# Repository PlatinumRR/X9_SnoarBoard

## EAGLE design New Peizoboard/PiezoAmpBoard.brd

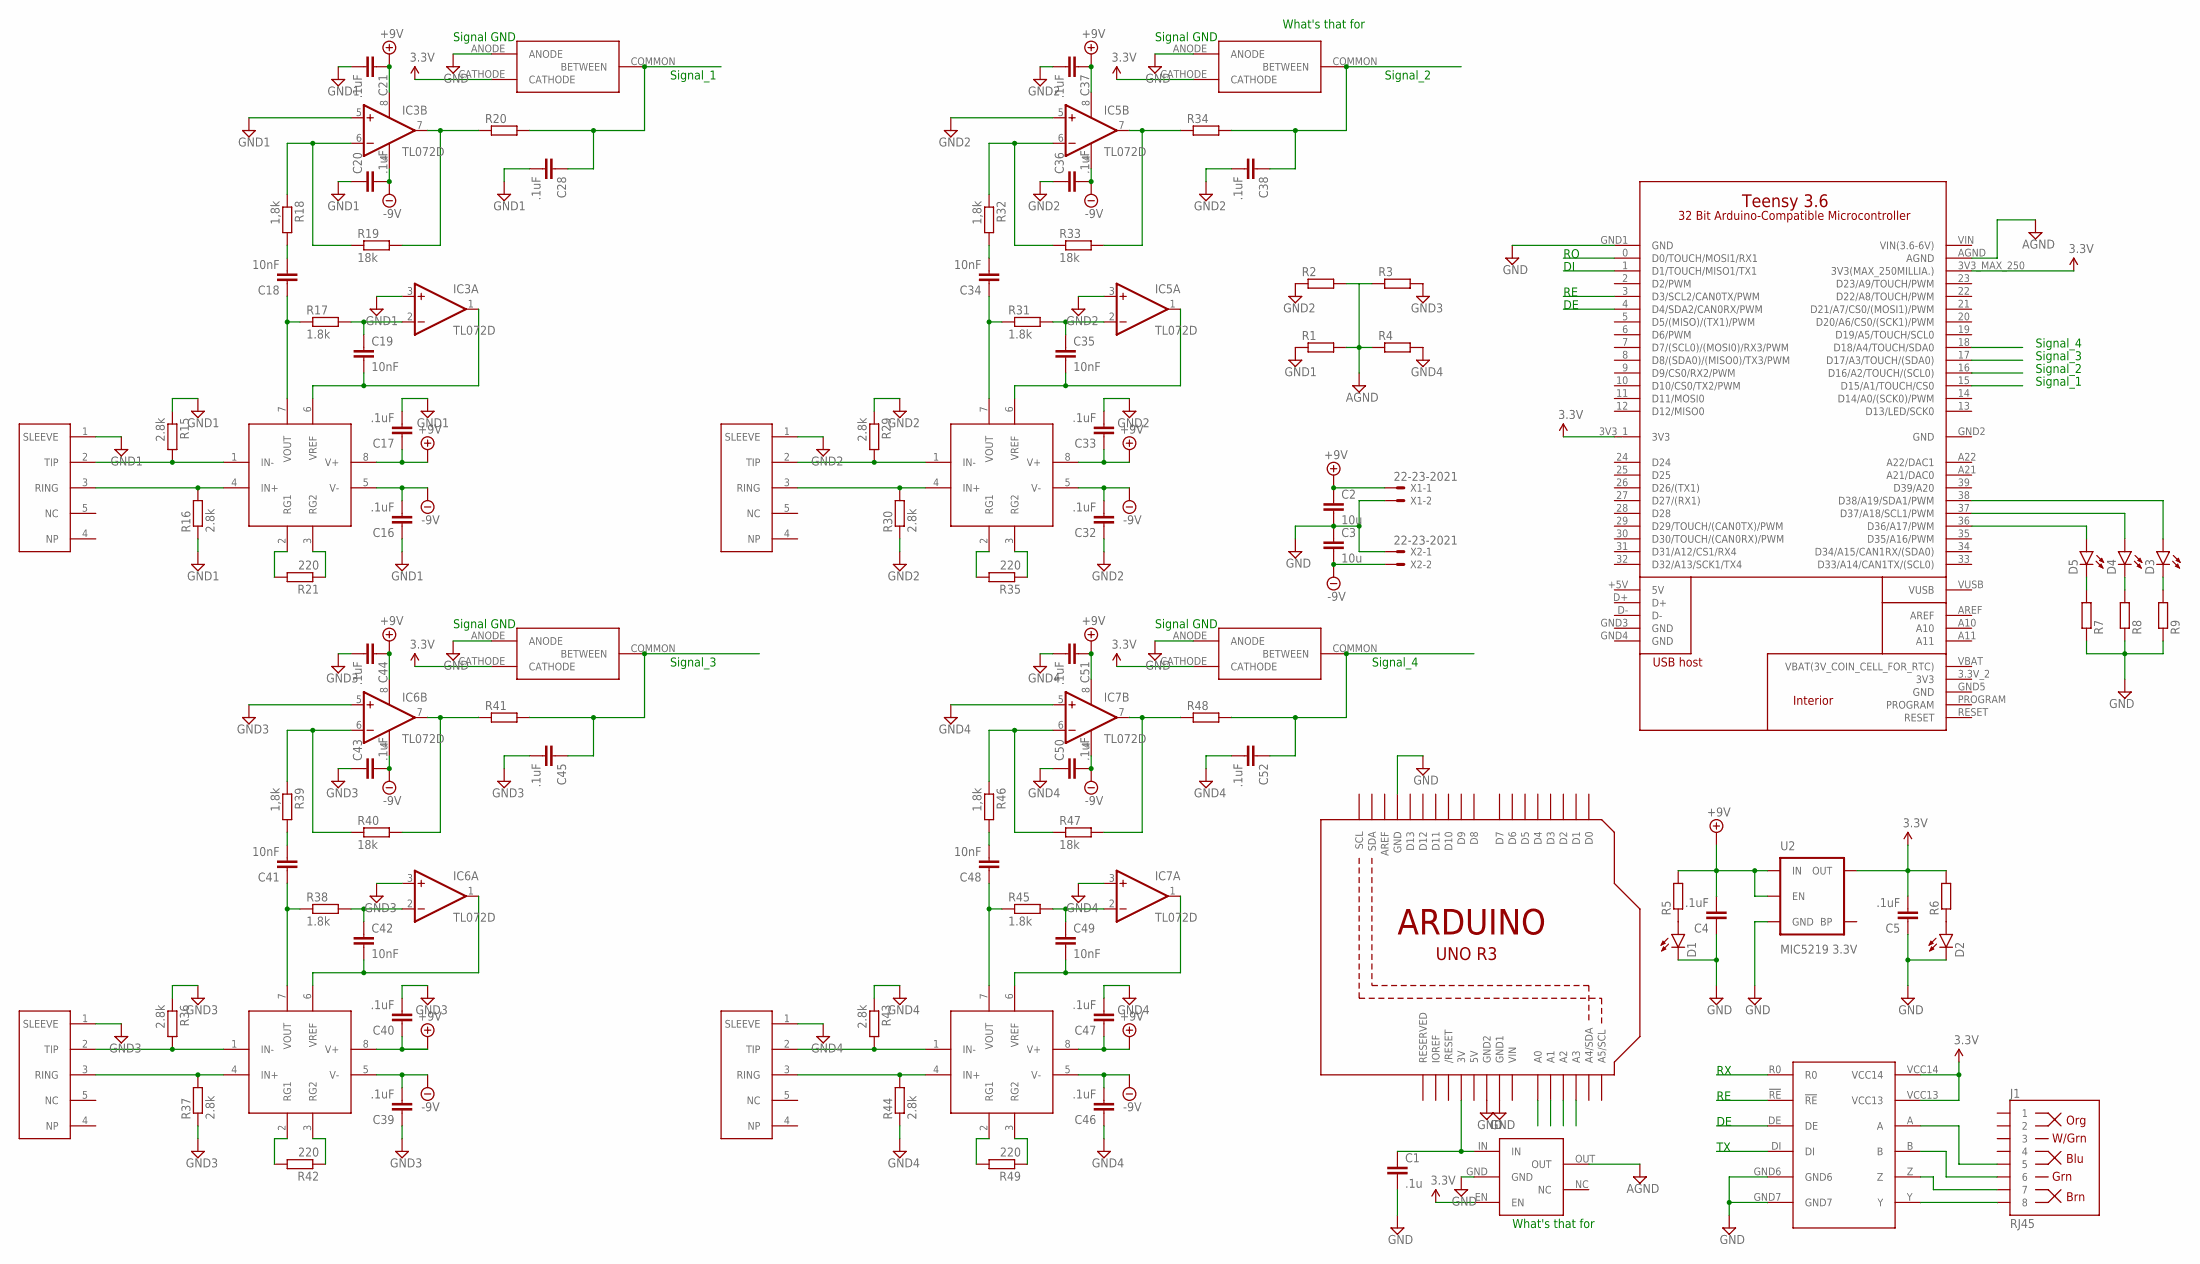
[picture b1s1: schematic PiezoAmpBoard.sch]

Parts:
C1: .1u; C0603
C2, C3: 10u; C0603
C4, C5, C16, C17, C20, C21, C28, C32, C33, C36, C37, C38, C39, C40, C43, C44, C45, C46, C47, C50, C51, C52: .1uF; C0603
C18, C19, C34, C35, C41, C42, C48, C49: 10nF; C0603
D1, D2, D3, D4, D5: LED0603; LED-0603
IC3, IC5, IC6, IC7: TL072D; SO08
J1: RJ45; RJ45-8
R1, R2, R3, R4, R5, R6, R7, R8, R9, R20, R34, R41, R48: R-EU_R0603; R0603
R15, R16, R29, R30, R36, R37, R43, R44: 2.8k; R0603
R17, R31, R38, R45: 1.8k; R0603
R18, R32, R39, R46: 1,8k; R0603
R19, R33, R40, R47: 18k; R0603
R21, R35, R42, R49: 220; R0603
U1: ARDUINOR3-BPLACE
U2: MIC5219 3.3V; SOT23-5
U$1: TPS76316; PDSO
U$2: TEENSY-3.6_ONLY_HOLES
U$3: MAX3491
U$4, U$14, U$17, U$20: AD82216; SOIC08
U$6, U$15, U$18, U$21: BAV99T; SOT-523
U$11, U$16, U$19, U$22: 3MMJACK; 1X05
X1, X2: 22-23-2021

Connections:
3.3V: C1.1, C5.2, R6.2, U1.3V, U2.5 (OUT), U$1.EN, U$1.IN, U$2.3V3_1 (3V3), U$2.3V3_MAX_250 (3V3(MAX_250MILLIA.)), U$3.VCC13, U$3.VCC14, U$6.CATHODE, U$15.CATHODE, U$18.CATHODE, U$21.CATHODE
5V: U1.5V
+9V: C4.2, R5.2, U2.1 (IN), U2.3 (EN)
AGND: R1.2, R2.2, R3.1, R4.1, U$1.OUT, U$2.AGND
DE: U$3.DE
GND: C1.2, C2.2, C3.1, C4.1, C5.1, D1.C, D2.C, R7.1, R8.1, R9.1, U1.GND, U1.GND1, U1.GND2, U2.2 (GND), U$1.GND, U$2.GND1 (GND), U$2.GND2 (GND), U$3.GND6, U$3.GND7, U$6.ANODE, U$15.ANODE, U$18.ANODE, U$21.ANODE, X1.2, X2.1
GND1: C16.1, C17.2, C20.1, C21.2, C28.2, IC3.3 (+IN), IC3.5 (+IN), R1.1, R15.1, R16.1, U$11.1 (SLEEVE)
GND2: C32.1, C33.2, C36.1, C37.2, C38.2, IC5.3 (+IN), IC5.5 (+IN), R2.1, R29.1, R30.1, U$16.1 (SLEEVE)
GND3: C39.1, C40.2, C43.1, C44.2, C45.2, IC6.3 (+IN), IC6.5 (+IN), R3.2, R36.1, R37.1, U$19.1 (SLEEVE)
GND4: C46.1, C47.2, C50.1, C51.2, C52.2, IC7.3 (+IN), IC7.5 (+IN), R4.2, R43.1, R44.1, U$22.1 (SLEEVE)
unnamed: D1.A, R5.1
unnamed: D2.A, R6.1
unnamed: D3.A, U$2.38 (D38/A19/SDA1/PWM)
unnamed: D4.A, U$2.37 (D37/A18/SCL1/PWM)
unnamed: D5.A, U$2.36 (D36/A17/PWM)
unnamed: D3.C, R9.2
unnamed: D4.C, R8.2
unnamed: D5.C, R7.2
unnamed: J1.8, U$3.Y
unnamed: J1.7, U$3.Z
unnamed: J1.6, U$3.B
unnamed: J1.5, U$3.A
unnamed: R15.2, U$4.1 (IN-), U$11.2 (TIP)
unnamed: R16.2, U$4.4 (IN+), U$11.3 (RING)
unnamed: R21.2, U$4.2 (RG1)
unnamed: R21.1, U$4.3 (RG2)
unnamed: C18.1, R17.1, U$4.7 (VOUT)
unnamed: C19.1, IC3.2 (-IN), R17.2
unnamed: IC3.7 (OUT), R19.2, R20.1
unnamed: C18.2, R18.2
unnamed: IC3.6 (-IN), R18.1, R19.1
unnamed: R29.2, U$14.1 (IN-), U$16.2 (TIP)
unnamed: R30.2, U$14.4 (IN+), U$16.3 (RING)
unnamed: R35.2, U$14.2 (RG1)
unnamed: R35.1, U$14.3 (RG2)
unnamed: C34.1, R31.1, U$14.7 (VOUT)
unnamed: C35.1, IC5.2 (-IN), R31.2
unnamed: IC5.7 (OUT), R33.2, R34.1
unnamed: C34.2, R32.2
unnamed: IC5.6 (-IN), R32.1, R33.1
unnamed: R36.2, U$17.1 (IN-), U$19.2 (TIP)
unnamed: R37.2, U$17.4 (IN+), U$19.3 (RING)
unnamed: R42.2, U$17.2 (RG1)
unnamed: R42.1, U$17.3 (RG2)
unnamed: C41.1, R38.1, U$17.7 (VOUT)
unnamed: C42.1, IC6.2 (-IN), R38.2
unnamed: IC6.7 (OUT), R40.2, R41.1
unnamed: C41.2, R39.2
unnamed: IC6.6 (-IN), R39.1, R40.1
unnamed: R43.2, U$20.1 (IN-), U$22.2 (TIP)
unnamed: R44.2, U$20.4 (IN+), U$22.3 (RING)
unnamed: R49.2, U$20.2 (RG1)
unnamed: R49.1, U$20.3 (RG2)
unnamed: C48.1, R45.1, U$20.7 (VOUT)
unnamed: C49.1, IC7.2 (-IN), R45.2
unnamed: IC7.7 (OUT), R47.2, R48.1
unnamed: C48.2, R46.2
unnamed: IC7.6 (-IN), R46.1, R47.1
PEIZOIN1: C28.1, R20.2, U1.A0, U$2.15 (D15/A1/TOUCH/CS0), U$6.COMMON (BETWEEN)
PEIZOIN2: C38.1, R34.2, U1.A1, U$2.16 (D16/A2/TOUCH/(SCL0)), U$15.COMMON (BETWEEN)
PEIZOIN3: C45.1, R41.2, U1.A2, U$2.17 (D17/A3/TOUCH/(SDA0)), U$18.COMMON (BETWEEN)
PEIZOIN4: C52.1, R48.2, U1.A3, U$2.18 (D18/A4/TOUCH/SDA0), U$21.COMMON (BETWEEN)
RE: U$2.3 (D3/SCL2/CAN0TX/PWM), U$2.4 (D4/SDA2/CAN0RX/PWM), U$3.!RE
RX: U$2.0 (D0/TOUCH/MOSI1/RX1), U$3.R0
TX: U$2.1 (D1/TOUCH/MISO1/TX1), U$3.DI
VIN: U1.VIN
VIN(3.6-6V): U$2.VIN (VIN(3.6-6V))
VREF2: C19.2, IC3.1 (OUT), U$4.6 (VREF)
VREF4: C35.2, IC5.1 (OUT), U$14.6 (VREF)
VREF5: C42.2, IC6.1 (OUT), U$17.6 (VREF)
VREF6: C49.2, IC7.1 (OUT), U$20.6 (VREF)
VS+1: C2.1, C17.1, C21.1, C33.1, C37.1, C40.1, C44.1, C47.1, C51.1, IC3.8 (V+), IC5.8 (V+), IC6.8 (V+), IC7.8 (V+), U$4.8 (V+), U$14.8 (V+), U$17.8 (V+), U$20.8 (V+), X1.1
VS-: C3.2, C16.2, C20.2, C32.2, C36.2, C39.2, C43.2, C46.2, C50.2, IC3.4 (V-), IC5.4 (V-), IC6.4 (V-), IC7.4 (V-), U$4.5 (V-), U$14.5 (V-), U$17.5 (V-), U$20.5 (V-), X2.2

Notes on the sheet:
Signal_1
Signal_2
Signal_3
Signal_4
Signal GND
What's that for

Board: 2 copper layers, 99 parts (0 on the bottom side), 69 nets, no tracks yet.

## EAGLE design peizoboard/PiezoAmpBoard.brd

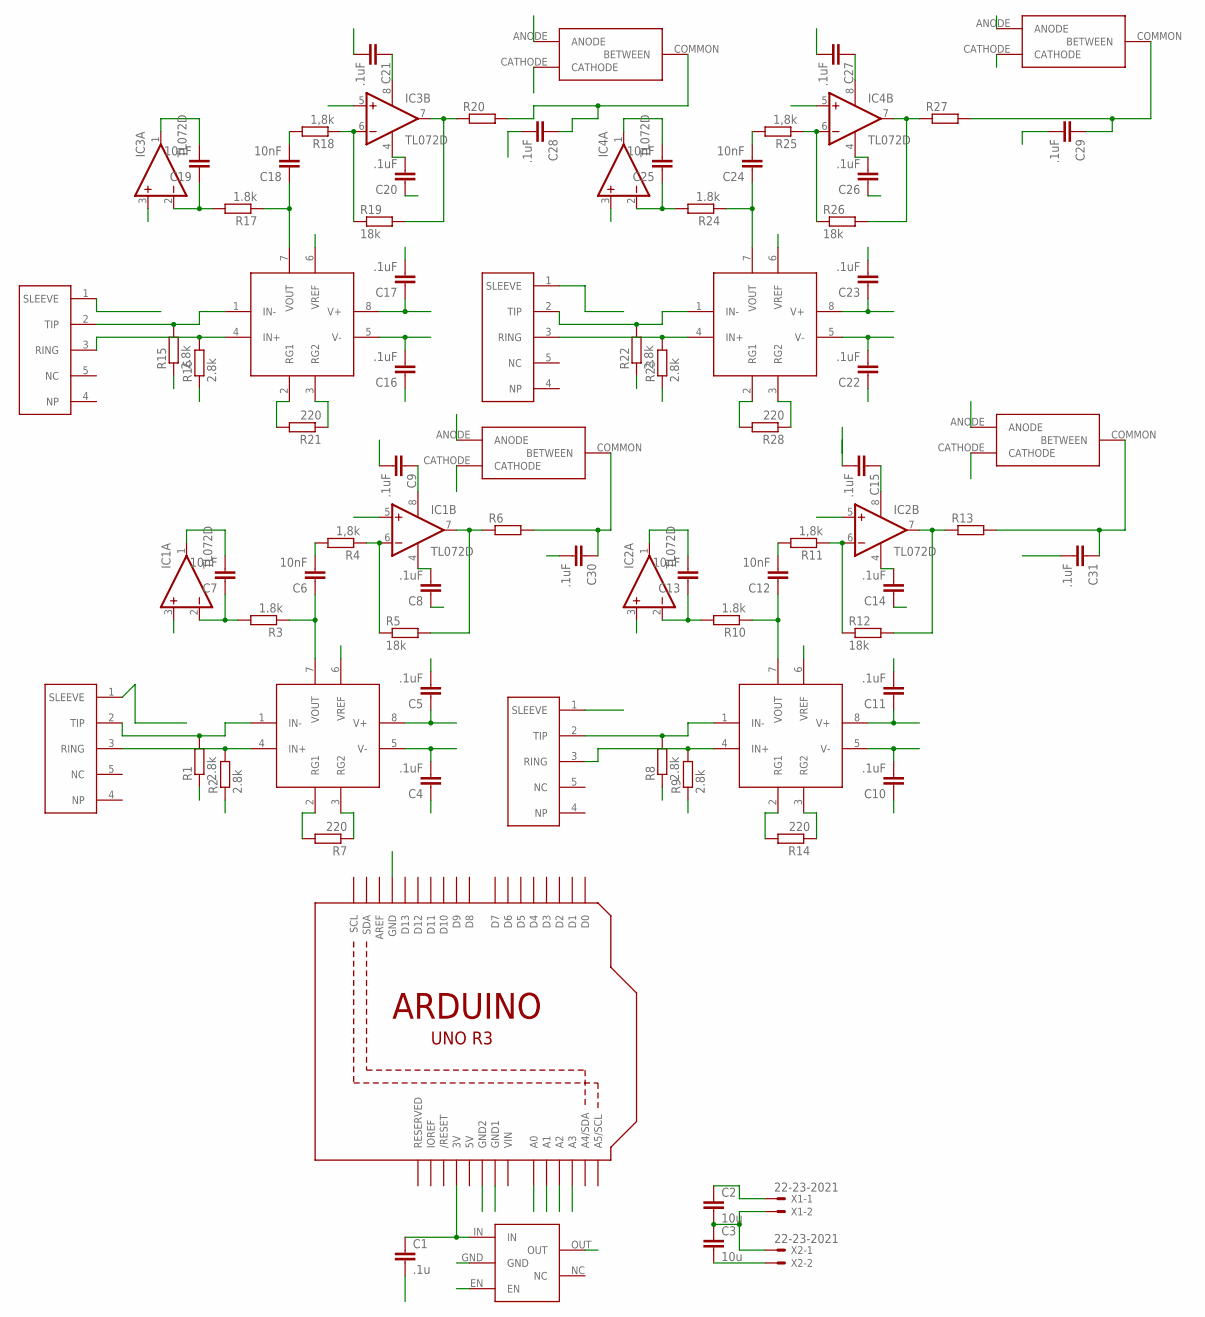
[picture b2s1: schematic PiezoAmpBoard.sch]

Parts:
C1: .1u; C0603
C2, C3: 10u; C0603
C4, C5, C8, C9, C10, C11, C14, C15, C16, C17, C20, C21, C22, C23, C26, C27, C28, C29, C30, C31: .1uF; C0603
C6, C7, C12, C13, C18, C19, C24, C25: 10nF; C0603
IC1, IC2, IC3, IC4: TL072D; SO08
R1, R2, R8, R9, R15, R16, R22, R23: 2.8k; R0603
R3, R10, R17, R24: 1.8k; R0603
R4, R11, R18, R25: 1,8k; R0603
R5, R12, R19, R26: 18k; R0603
R6, R13, R20, R27: R-EU_R0603; R0603
R7, R14, R21, R28: 220; R0603
U1: ARDUINOR3-BPLACE
U$1: TPS76316; PDSO
U$2, U$3, U$4, U$5: AD82216; SOIC08
U$6, U$7, U$8, U$9: BAV99T; SOT-523
U$10, U$11, U$12, U$13: 3MMJACK; 1X05
X1, X2: 22-23-2021

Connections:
3.3V: C1.1, U1.3V, U$1.EN, U$1.IN, U$6.CATHODE, U$7.CATHODE, U$8.CATHODE, U$9.CATHODE
5V: U1.5V
GND: C1.2, U1.GND, U1.GND1, U1.GND2, U$1.GND, U$6.ANODE, U$7.ANODE, U$8.ANODE, U$9.ANODE
unnamed: R7.2, U$2.2 (RG1)
unnamed: R1.2, U$2.1 (IN-), U$10.2 (TIP)
unnamed: R2.2, U$2.4 (IN+), U$10.3 (RING)
unnamed: R7.1, U$2.3 (RG2)
unnamed: C6.1, R3.1, U$2.7 (VOUT)
unnamed: C7.1, IC1.2 (-IN), R3.2
unnamed: IC1.7 (OUT), R5.2, R6.1
unnamed: R8.2, U$3.1 (IN-), U$13.2 (TIP)
unnamed: C6.2, R4.2
unnamed: IC1.6 (-IN), R4.1, R5.1
unnamed: R9.2, U$3.4 (IN+), U$13.3 (RING)
unnamed: R14.2, U$3.2 (RG1)
unnamed: R14.1, U$3.3 (RG2)
unnamed: C12.1, R10.1, U$3.7 (VOUT)
unnamed: C13.1, IC2.2 (-IN), R10.2
unnamed: IC2.7 (OUT), R12.2, R13.1
unnamed: C12.2, R11.2
unnamed: IC2.6 (-IN), R11.1, R12.1
unnamed: R15.2, U$4.1 (IN-), U$11.2 (TIP)
unnamed: R16.2, U$4.4 (IN+), U$11.3 (RING)
unnamed: R21.2, U$4.2 (RG1)
unnamed: R21.1, U$4.3 (RG2)
unnamed: C18.1, R17.1, U$4.7 (VOUT)
unnamed: C19.1, IC3.2 (-IN), R17.2
unnamed: IC3.7 (OUT), R19.2, R20.1
unnamed: C18.2, R18.2
unnamed: IC3.6 (-IN), R18.1, R19.1
unnamed: R22.2, U$5.1 (IN-), U$12.2 (TIP)
unnamed: R23.2, U$5.4 (IN+), U$12.3 (RING)
unnamed: R28.2, U$5.2 (RG1)
unnamed: R28.1, U$5.3 (RG2)
unnamed: C24.1, R24.1, U$5.7 (VOUT)
unnamed: C25.1, IC4.2 (-IN), R24.2
unnamed: IC4.7 (OUT), R26.2, R27.1
unnamed: C24.2, R25.2
unnamed: IC4.6 (-IN), R25.1, R26.1
PEIZOIN1: C28.1, R20.2, U1.A0, U$6.COMMON (BETWEEN)
PEIZOIN2: C29.1, R27.2, U1.A1, U$7.COMMON (BETWEEN)
PEIZOIN3: C31.1, R13.2, U1.A2, U$9.COMMON (BETWEEN)
PEIZOIN4: C30.1, R6.2, U1.A3, U$8.COMMON (BETWEEN)
VGND: C2.2, C3.1, C4.1, C5.2, C8.1, C9.2, C10.1, C11.2, C14.1, C15.2, C16.1, C17.2, C20.1, C21.2, C22.1, C23.2, C26.1, C27.2, C28.2, C29.2, C30.2, C31.2, IC1.3 (+IN), IC1.5 (+IN), IC2.3 (+IN), IC2.5 (+IN), IC3.3 (+IN), IC3.5 (+IN), IC4.3 (+IN), IC4.5 (+IN), R1.1, R2.1, R8.1, R9.1, R15.1, R16.1, R22.1, R23.1, U$1.OUT, U$10.1 (SLEEVE), U$11.1 (SLEEVE), U$12.1 (SLEEVE), U$13.1 (SLEEVE), X1.2, X2.1
VIN: U1.VIN
VREF: C7.2, IC1.1 (OUT), U$2.6 (VREF)
VREF1: C13.2, IC2.1 (OUT), U$3.6 (VREF)
VREF2: C19.2, IC3.1 (OUT), U$4.6 (VREF)
VREF3: C25.2, IC4.1 (OUT), U$5.6 (VREF)
VS+: C2.1, C5.1, C9.1, C11.1, C15.1, C17.1, C21.1, C23.1, C27.1, IC1.8 (V+), IC2.8 (V+), IC3.8 (V+), IC4.8 (V+), U$2.8 (V+), U$3.8 (V+), U$4.8 (V+), U$5.8 (V+), X1.1
VS-: C3.2, C4.2, C8.2, C10.2, C14.2, C16.2, C20.2, C22.2, C26.2, IC1.4 (V-), IC2.4 (V-), IC3.4 (V-), IC4.4 (V-), U$2.5 (V-), U$3.5 (V-), U$4.5 (V-), U$5.5 (V-), X2.2

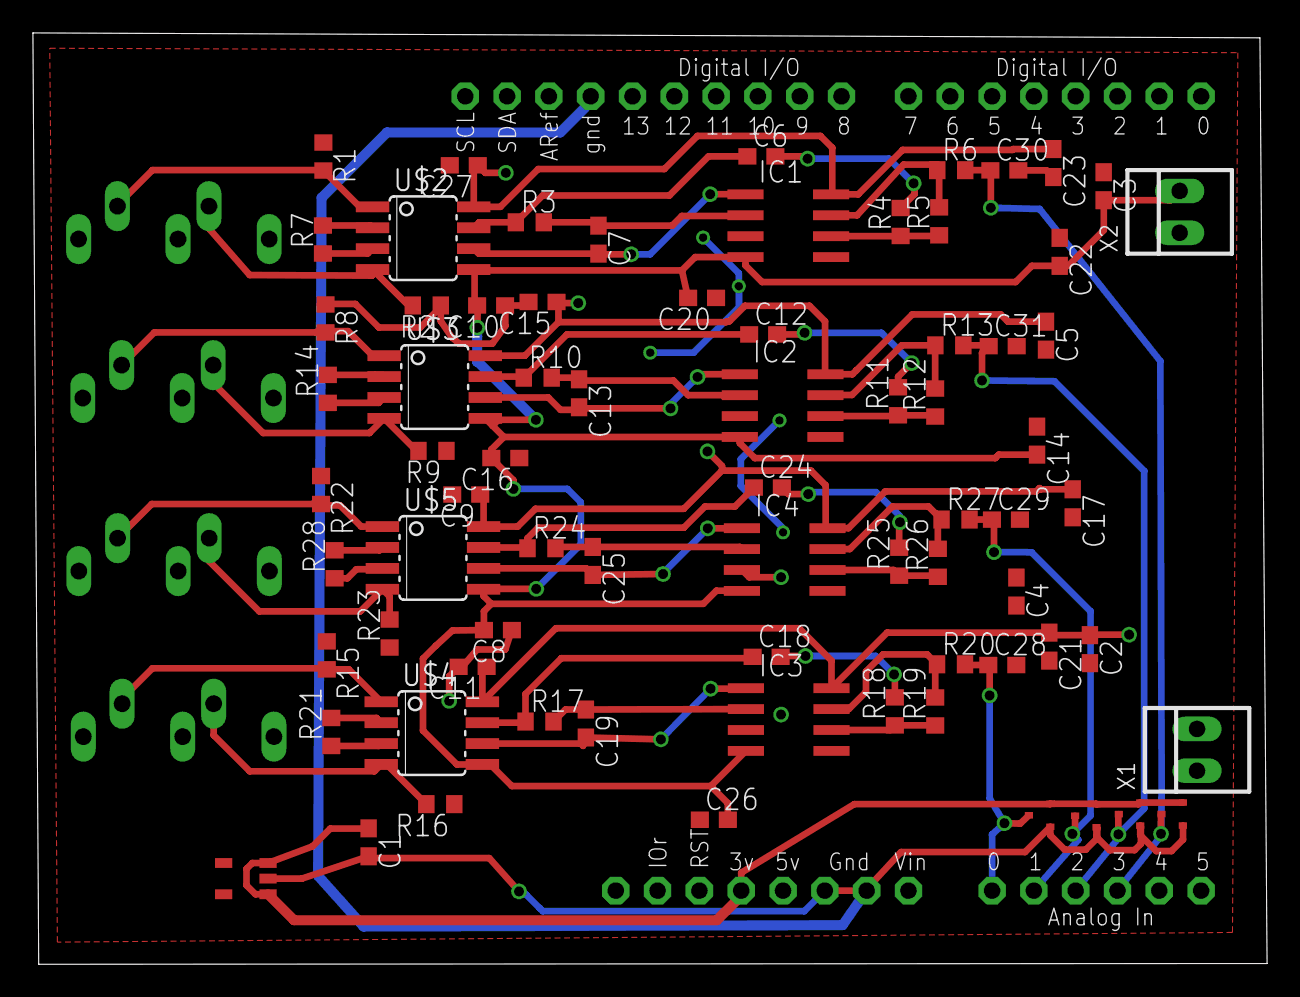
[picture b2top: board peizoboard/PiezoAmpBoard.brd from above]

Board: 2 copper layers, 75.0 x 56.6 mm, 79 parts (0 on the bottom side), 49 nets.

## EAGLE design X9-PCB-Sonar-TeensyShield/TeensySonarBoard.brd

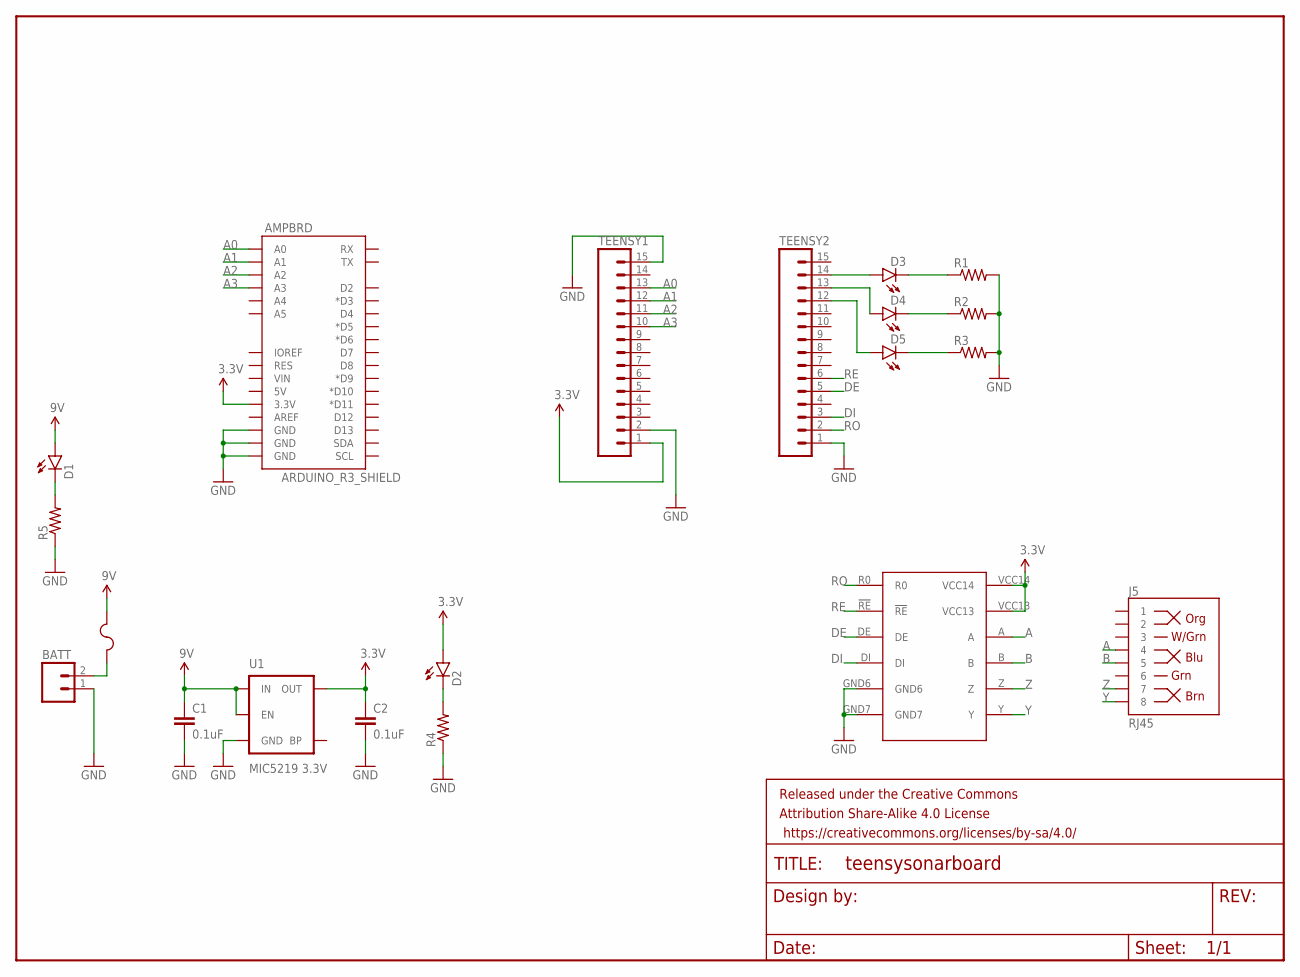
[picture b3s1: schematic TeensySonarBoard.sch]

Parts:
AMPBRD: ARDUINO_R3_SHIELD; UNO_R3_SHIELD
BATT: M02JST-PTH-VERT; JST-2-PTH-VERT
C1, C2: 0.1uF; 0603-CAP
D1, D2, D3, D4, D5: LED0603; LED-0603
F1: 2A; KEYSTONE_FUSE_3587
FRAME1: FRAME-LETTERNO_PACKAGE; DUMMY
J5: RJ45; RJ45-8
R1, R2, R3, R4, R5: R-US_R0603; R0603
TEENSY1, TEENSY2: M15; 1X15
U1: MIC5219 3.3V; SOT23-5
U$1: MAX3491

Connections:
3.3V: AMPBRD.3.3V, C2.1, D2.A, TEENSY1.1, U1.5 (OUT), U$1.VCC13, U$1.VCC14
A: J5.4, U$1.A
A0: AMPBRD.A0, TEENSY1.13
A1: AMPBRD.A1, TEENSY1.12
A2: AMPBRD.A2, TEENSY1.11
A3: AMPBRD.A3, TEENSY1.10
B: J5.5, U$1.B
DE: TEENSY2.5, U$1.DE
DI: TEENSY2.3, U$1.DI
GND: AMPBRD.GND@0 (GND), AMPBRD.GND@1 (GND), AMPBRD.GND@2 (GND), BATT.1, C1.2, C2.2, R1.2, R2.2, R3.2, R4.1, R5.1, TEENSY1.2, TEENSY1.15, TEENSY2.1, U1.2 (GND), U$1.GND6, U$1.GND7
unnamed: BATT.2, F1.P$1, F1.P$2
unnamed: D3.A, TEENSY2.14
unnamed: D4.A, TEENSY2.13
unnamed: D5.A, TEENSY2.12
unnamed: D1.C, R5.2
unnamed: D2.C, R4.2
unnamed: D3.C, R1.1
unnamed: D4.C, R2.1
unnamed: D5.C, R3.1
RE: TEENSY2.6, U$1.!RE
RO: TEENSY2.2, U$1.R0
VCC: C1.1, D1.A, F1.P$3, F1.P$4, U1.1 (IN), U1.3 (EN)
Y: J5.8, U$1.Y
Z: J5.7, U$1.Z

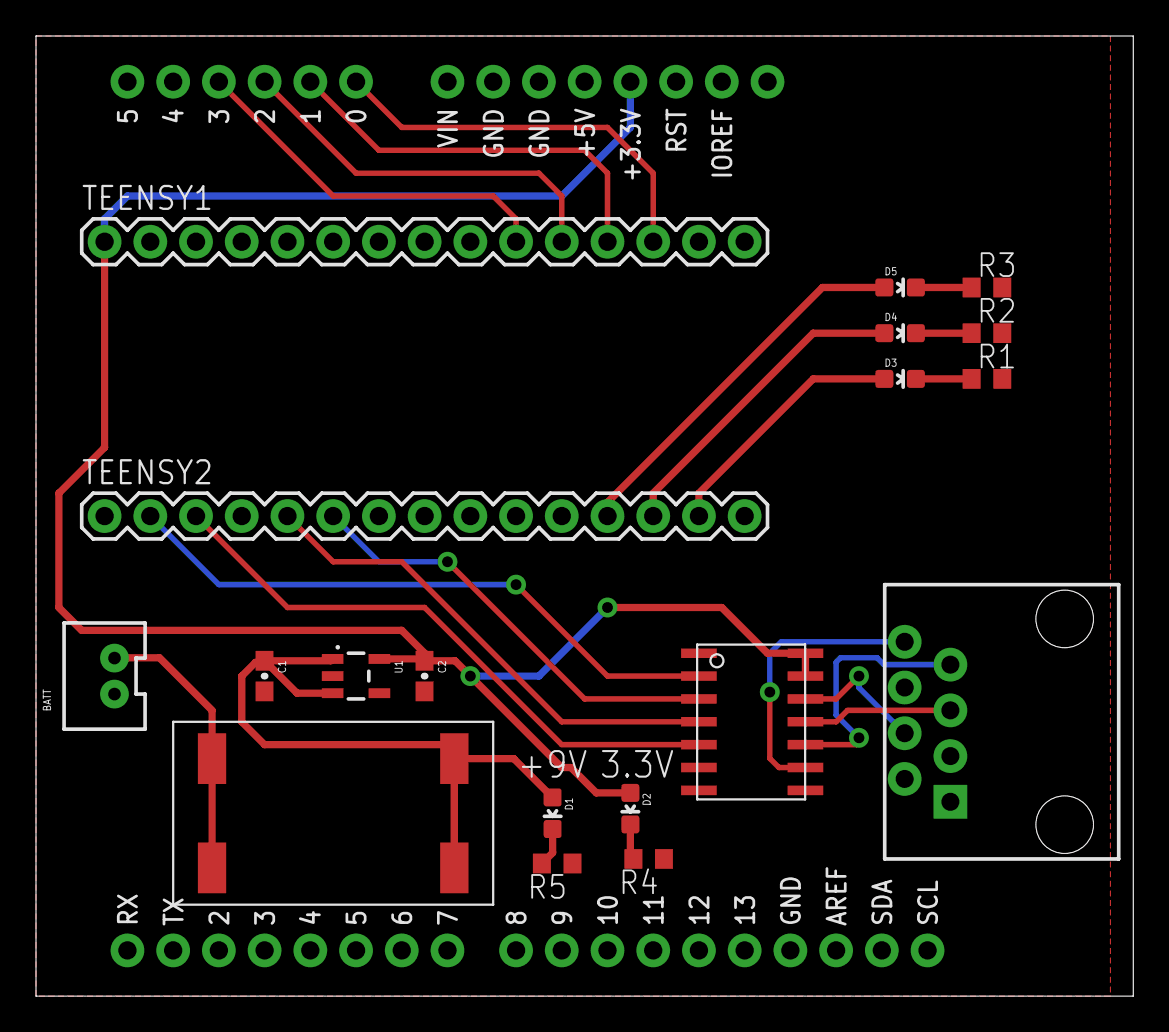
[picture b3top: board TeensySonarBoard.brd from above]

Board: 2 copper layers, 61.0 x 53.3 mm, 21 parts (0 on the bottom side), 24 nets.

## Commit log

2017-02-27 new upload
    new
2017-02-27 add 9v and 3v indicator LEDs
    From mac
2017-02-27 add 3 teensy indicator LEDs
    from pc
2017-02-27 Add all parts, still need some wires, need serial connection
    from pc
2017-03-01 add 2 question points
    From PC
2017-03-02 Compelete the serial connection
    From PC

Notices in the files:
parts and their libraries:
SparkFun-PowerIC: Licensing: Creative Commons ShareAlike 4.0 International - https://creativecommons.org/licenses/by-sa/4.0
SparkFun-Aesthetics: Released under the Creative Commons Attribution Share-Alike 4.0 License
SparkFun-Aesthetics: https://creativecommons.org/licenses/by-sa/4.0
